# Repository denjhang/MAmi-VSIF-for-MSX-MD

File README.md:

# MAmi-VSIF for MSX+MD
 The open source hardware implementation of the VSIF standard can be completed using the red FT232 module that can be easily purchased on Alex. No complicated welding is required. The current hardware supports both MSX and MD devices.    
 The currently supported software is VGM player and MamidiMEMO. For details, see here:   
 https://github.com/110-kenichi/mame  
## Connect to 1ChipMSX (clone)  
The latest version of the vgmplay program fully supports 1ChipMSX's PSG+OPLL+SCC1, but it needs to be used in a certain order to be used normally. First use mini usb to connect to the FTDI module, then open vgmplay. At this time, first check whether the words "usb serial port (com7)" appear in the device manager. If not, you need to install the driver.  
  
After the computer correctly recognizes FTDI, the next step is to open your 1ChipMSX, and then use sofarun to open VGMPlay_msx.rom and run the rom according to the default settings.  
At this time, msx will have a black screen background with "MAMI VGM Sound Driver", and then you can see that the OPLL and SCC of your 1ChipMSX have been correctly recognized and the device location is displayed. At this time, plug the DB9 female connector of VSIF into the JoyPort2 of 1ChipMSX, and the connection is successful without pressing any buttons.  
  
Then set the VSIF Checker according to the picture method. After the setting is completed, you can drag the vgm file into the VSIF Checker playlist. If the playback is very stuck, you need to adjust the FTDI CLK. I recommend adjusting it to 7/5/5. The playback speed is related to the length of the USB cable. It is not recommended to use a USB cable that is too long.    
    
It is best to use a new mini usb cable and avoid using old or rusty cables. Theoretically, the shorter the length of the USB cable, the faster the VSIF data transfer rate.

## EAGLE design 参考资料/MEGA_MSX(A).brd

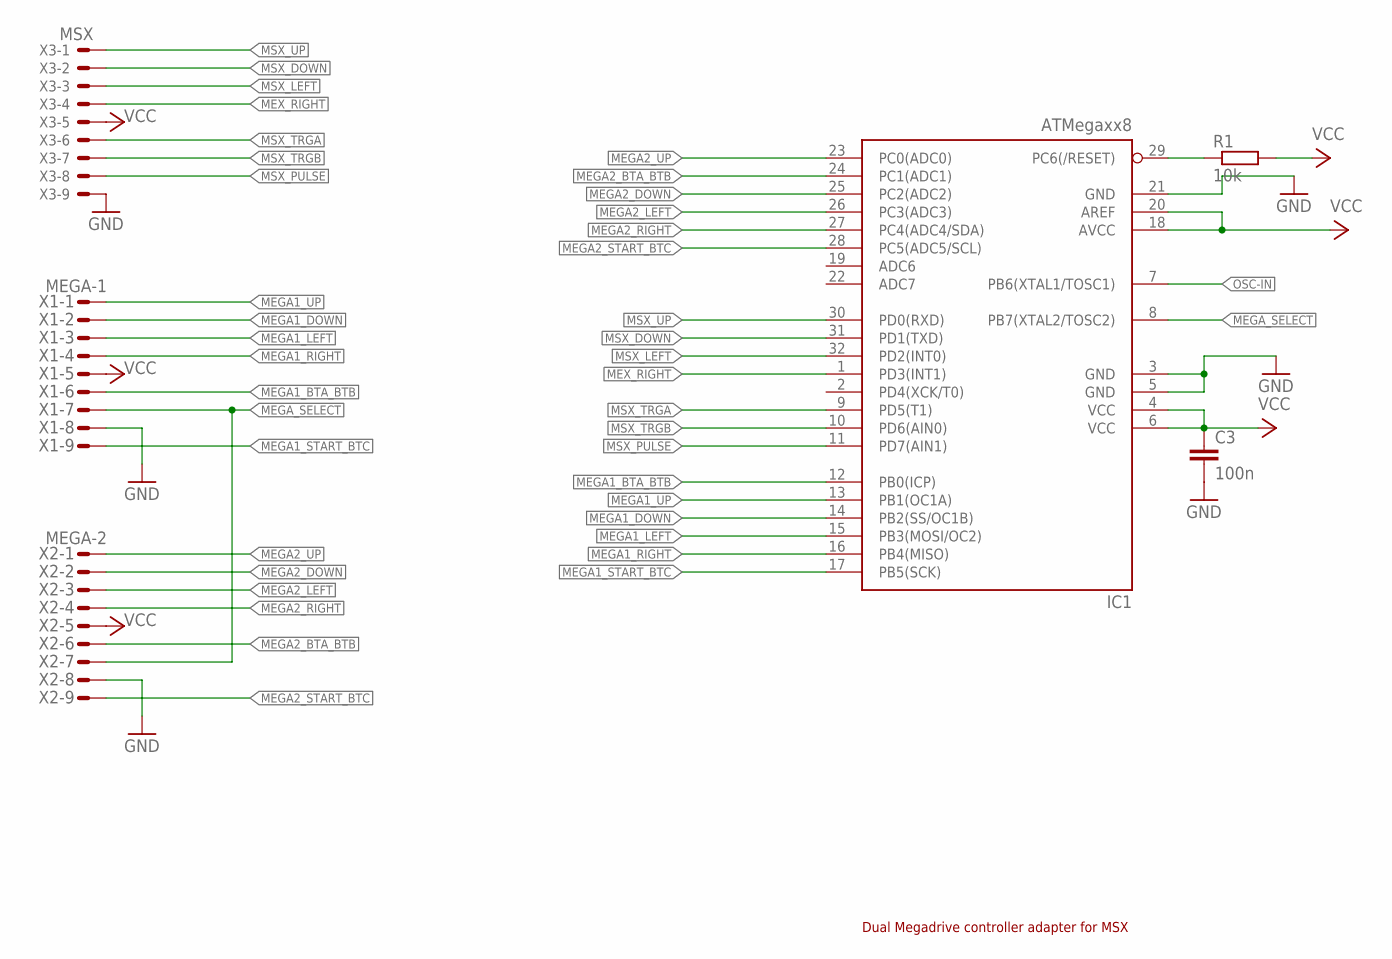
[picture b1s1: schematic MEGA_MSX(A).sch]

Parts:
C3: 100n; C0805
IC1: ATMegaxx8; TQFP32-08
R1: 10k; R0805
X1: MEGA-1; M09D
X2: MEGA-2; M09D
X3: MSX; 22-23-2091

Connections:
!RESET: IC1.29 (PC6(/RESET)), R1.1
GND: C3.2, IC1.3 (GND), IC1.5 (GND), IC1.21 (GND), X1.8, X2.8, X3.9
MEGA1_BTA_BTB: IC1.12 (PB0(ICP)), X1.6
MEGA1_DOWN: IC1.14 (PB2(SS/OC1B)), X1.2
MEGA1_LEFT: IC1.15 (PB3(MOSI/OC2)), X1.3
MEGA1_RIGHT: IC1.16 (PB4(MISO)), X1.4
MEGA1_START_BTC: IC1.17 (PB5(SCK)), X1.9
MEGA1_UP: IC1.13 (PB1(OC1A)), X1.1
MEGA2_BTA_BTB: IC1.24 (PC1(ADC1)), X2.6
MEGA2_DOWN: IC1.25 (PC2(ADC2)), X2.2
MEGA2_LEFT: IC1.26 (PC3(ADC3)), X2.3
MEGA2_RIGHT: IC1.27 (PC4(ADC4/SDA)), X2.4
MEGA2_START_BTC: IC1.28 (PC5(ADC5/SCL)), X2.9
MEGA2_UP: IC1.23 (PC0(ADC0)), X2.1
MEGA_SELECT: IC1.8 (PB7(XTAL2/TOSC2)), X1.7, X2.7
MEX_RIGHT: IC1.1 (PD3(INT1)), X3.4
MSX_DOWN: IC1.31 (PD1(TXD)), X3.2
MSX_LEFT: IC1.32 (PD2(INT0)), X3.3
MSX_PULSE: IC1.11 (PD7(AIN1)), X3.8
MSX_TRGA: IC1.9 (PD5(T1)), X3.6
MSX_TRGB: IC1.10 (PD6(AIN0)), X3.7
MSX_UP: IC1.30 (PD0(RXD)), X3.1
OSC-IN: IC1.7 (PB6(XTAL1/TOSC1))
VCC: C3.1, IC1.4 (VCC), IC1.6 (VCC), IC1.18 (AVCC), IC1.20 (AREF), R1.2, X1.5, X2.5, X3.5

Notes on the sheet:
Dual Megadrive controller adapter for MSX

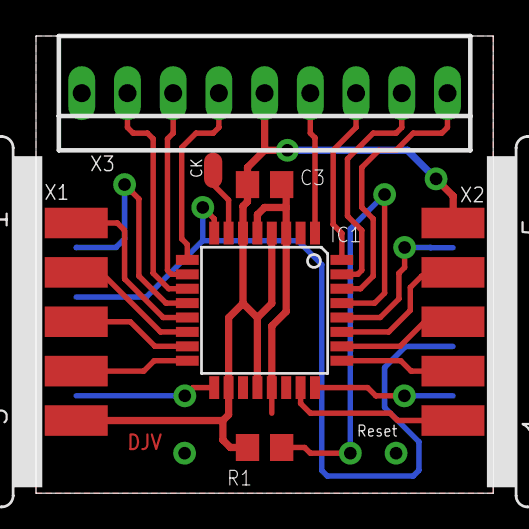
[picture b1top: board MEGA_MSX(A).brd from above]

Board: 2 copper layers, 25.4 x 25.4 mm, 6 parts (0 on the bottom side), 23 nets.

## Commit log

2024-05-18 2024.5.18
2024-05-19 add rom
2024-05-19 add setting
2024-05-19 add driver
